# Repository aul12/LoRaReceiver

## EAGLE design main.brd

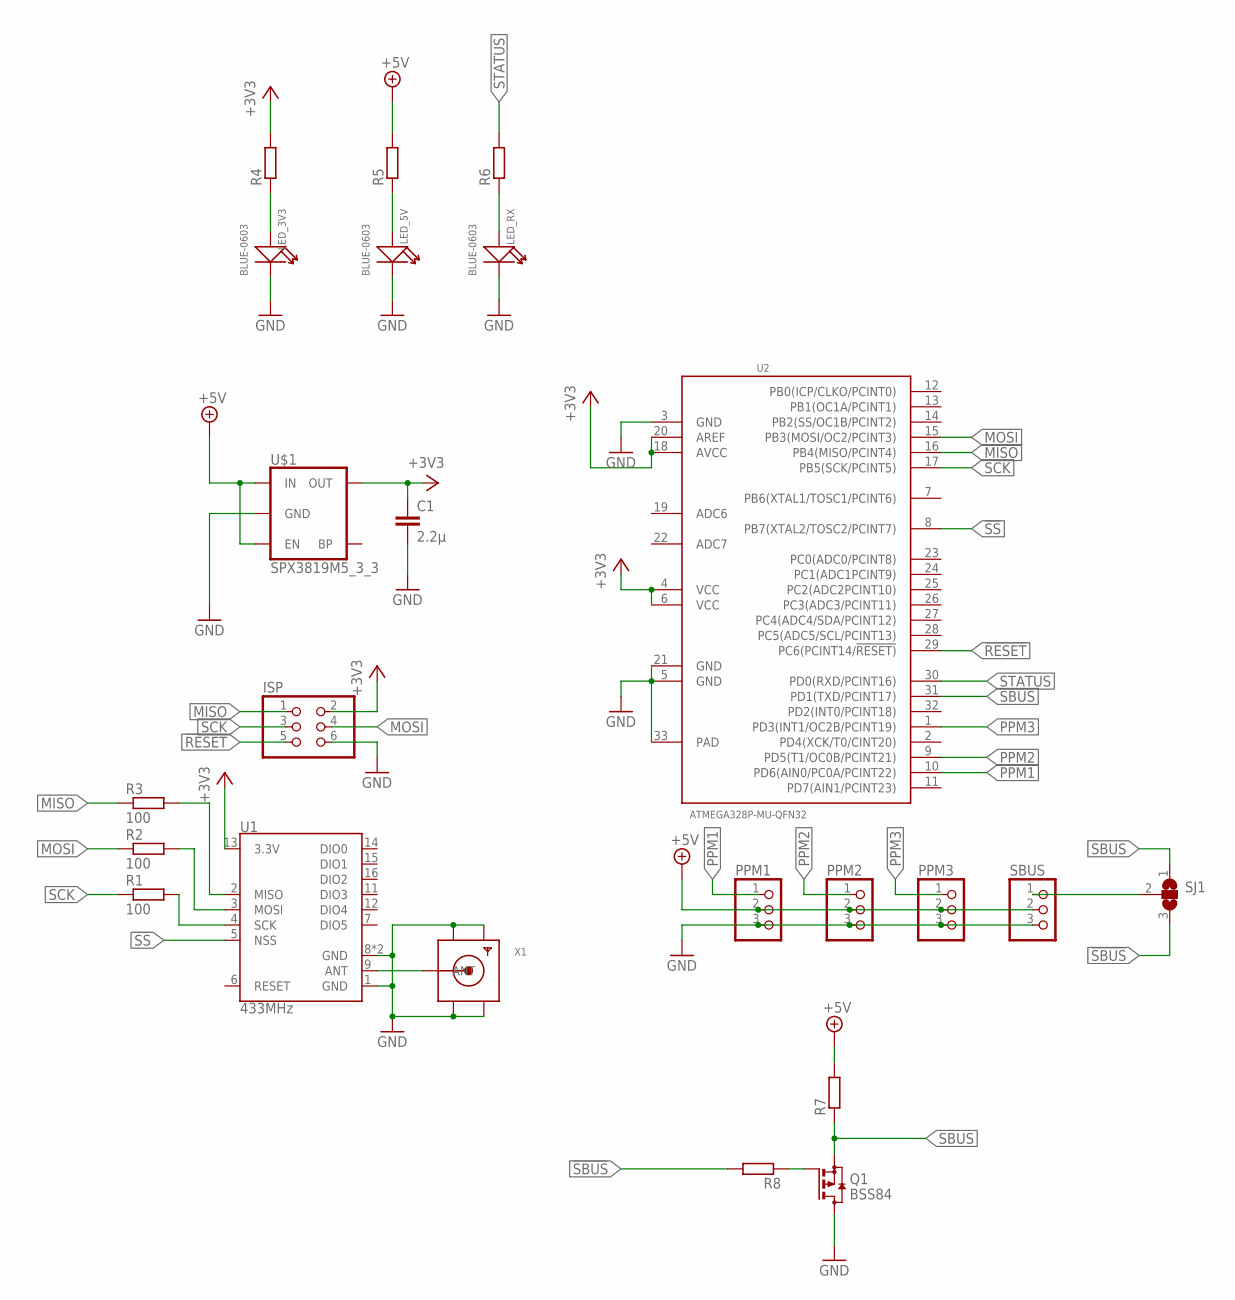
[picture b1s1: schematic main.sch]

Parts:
C1: 2.2µ; C0603
ISP: PINHD-2X3_2.54-SMD; 2X03SMD
LED_3V3, LED_5V: BLUE-0603; LED-0603
LED_RX: BLUE-0603; LED-0603
PPM1, PPM2, PPM3: PINHD-1X3_2.54-SMD; 1X03SMD
Q1: BSS84; SOT23
R1, R2, R3: 100; R0603
R4, R5, R6, R7, R8: R-EU_R0603; R0603
SBUS: PINHD-1X3_2.54-SMD; 1X03SMD
SJ1: SJ2W; SJ_2
U1: 433MHz; RFM69HCW-XXXS2
U2: ATMEGA328P-MU-QFN32; QFN32G-0.5-5X5MM
U$1: SPX3819M5_3_3; SOT23-5
X1: SMACONNECTOR_EDGE; SMA_EDGELAUNCH

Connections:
!RESET: ISP.5, U2.29 (PC6(PCINT14/!RESET))
!SBUS: R8.2, SJ1.3, U2.31 (PD1(TXD/PCINT17))
!SS: U1.5 (NSS), U2.8 (PB7(XTAL2/TOSC2/PCINT7))
+3V3: C1.1, ISP.2, R4.2, U1.13 (3.3V), U2.4 (VCC), U2.6 (VCC), U2.18 (AVCC), U2.20 (AREF), U$1.5 (OUT)
+5V: PPM1.2, PPM2.2, PPM3.2, R5.2, R7.2, SBUS.2, U$1.1 (IN), U$1.3 (EN)
GND: C1.2, ISP.6, LED_3V3.-, LED_5V.-, LED_RX.-, PPM1.3, PPM2.3, PPM3.3, Q1.3 (D), SBUS.3, U1.1 (GND), U1.8 (GND), U1.10 (GND), U2.3 (GND), U2.5 (GND), U2.21 (GND), U2.33 (PAD), U$1.2 (GND), X1.GND@1 (GND4), X1.GND@2 (GND3), X1.GND@3 (GND2), X1.GND@4 (GND1)
MISO: ISP.1, R3.1, U2.16 (PB4(MISO/PCINT4))
MOSI: ISP.4, R2.1, U2.15 (PB3(MOSI/OC2/PCINT3))
unnamed: U1.9 (ANT), X1.P (ANT)
unnamed: R1.2, U1.4 (SCK)
unnamed: R2.2, U1.3 (MOSI)
unnamed: R3.2, U1.2 (MISO)
unnamed: LED_RX.+, R6.1
unnamed: SBUS.1, SJ1.2
unnamed: LED_3V3.+, R4.1
unnamed: LED_5V.+, R5.1
unnamed: Q1.1 (G), R8.1
PPM1: PPM1.1, U2.10 (PD6(AIN0/PC0A/PCINT22))
PPM2: PPM2.1, U2.9 (PD5(T1/OC0B/PCINT21))
PPM3: PPM3.1, U2.1 (PD3(INT1/OC2B/PCINT19))
SBUS: Q1.2 (S), R7.1, SJ1.1
SCK: ISP.3, R1.1, U2.17 (PB5(SCK/PCINT5))
STATUS: R6.2, U2.30 (PD0(RXD/PCINT16))

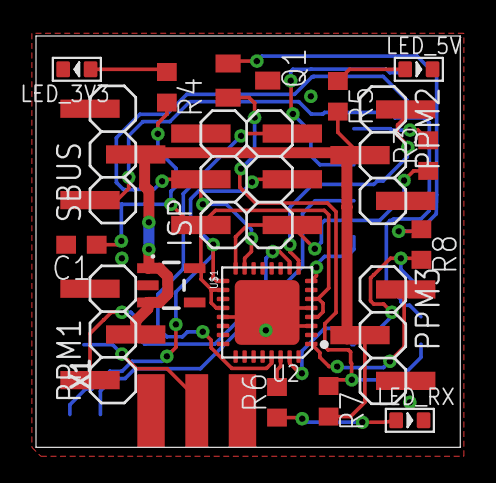
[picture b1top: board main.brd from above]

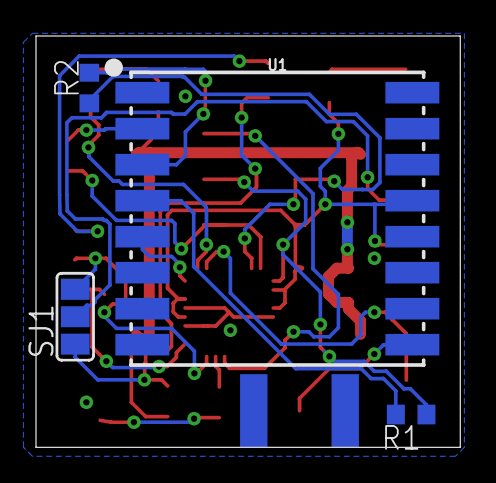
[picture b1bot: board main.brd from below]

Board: 2 copper layers, 23.6 x 22.9 mm, 23 parts (4 on the bottom side), 23 nets.

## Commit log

2018-04-11 Redesign
2018-04-11 Cleanup
2018-04-12 design rules
2018-04-12 Layout cleanup
2018-04-12 Started redesign
2018-04-12 Adapted to the new design rules
2018-05-03 Moved SMA Connector
2018-05-03 Starting fixing all DRC issues, only GND issues left
2018-05-05 Changed some pins to simplify the layout

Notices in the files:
parts and their libraries:
SparkFun-RF: Licensing: Creative Commons ShareAlike 4.0 International - https://creativecommons.org/licenses/by-sa/4.0
